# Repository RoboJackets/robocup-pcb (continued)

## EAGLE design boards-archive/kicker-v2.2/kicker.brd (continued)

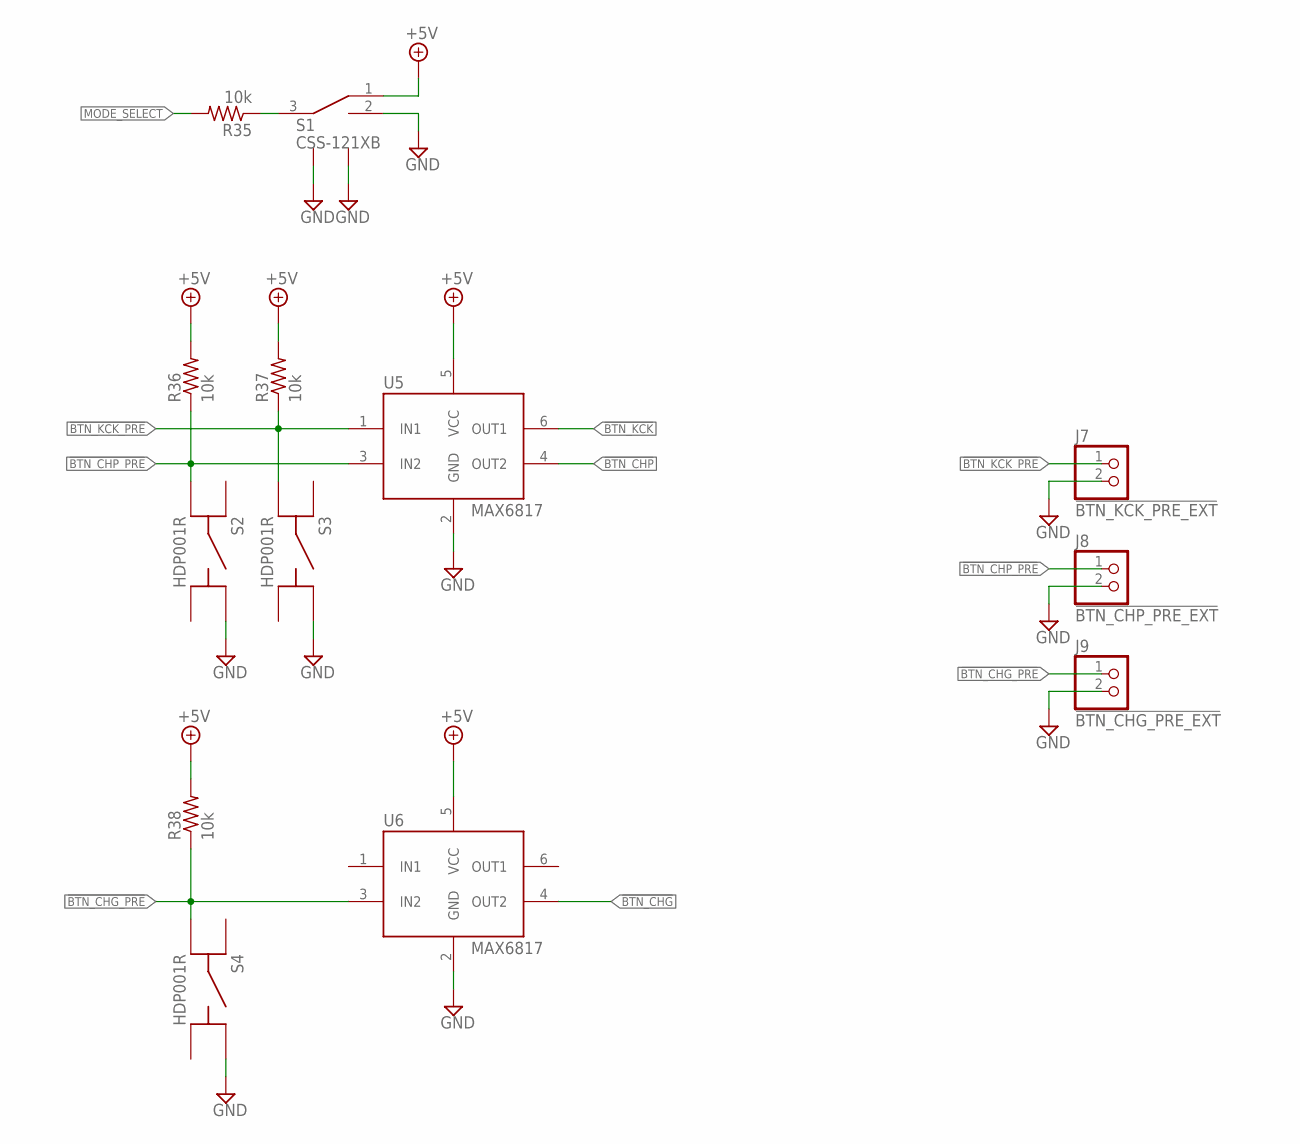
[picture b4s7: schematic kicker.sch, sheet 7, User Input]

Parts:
J7: !BTN_KCK_PRE_EXT; 1X2
J8: !BTN_CHP_PRE_EXT; 1X2
J9: !BTN_CHG_PRE_EXT; 1X2
R35, R36, R37, R38: 10k; R0603
S1: CSS-121XB
S2, S3, S4: HDP001R
U5, U6: MAX6817; SOT-23-6

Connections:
!BTN_CHG: U6.4 (OUT2); also elsewhere on the board
!BTN_CHG_PRE: J9.1, R38.1, S4.C (A2), U6.3 (IN2)
!BTN_CHP: U5.4 (OUT2); also elsewhere on the board
!BTN_CHP_PRE: J8.1, R36.1, S2.C (A2), U5.3 (IN2)
!BTN_KCK: U5.6 (OUT1); also elsewhere on the board
!BTN_KCK_PRE: J7.1, R37.1, S3.C (A2), U5.1 (IN1)
+5V: R36.2, R37.2, R38.2, S1.1 (A), U5.5 (VCC), U6.5 (VCC); also elsewhere on the board
GND: J7.2, J8.2, J9.2, S1.2 (B), S1.LEG1, S1.LEG4 (LEG2), S2.B (B1), S3.B (B1), S4.B (B1), U5.2 (GND), U6.2 (GND); also elsewhere on the board
MODE_SELECT: R35.2; also elsewhere on the board
unnamed: R35.1, S1.3 (COMMON)

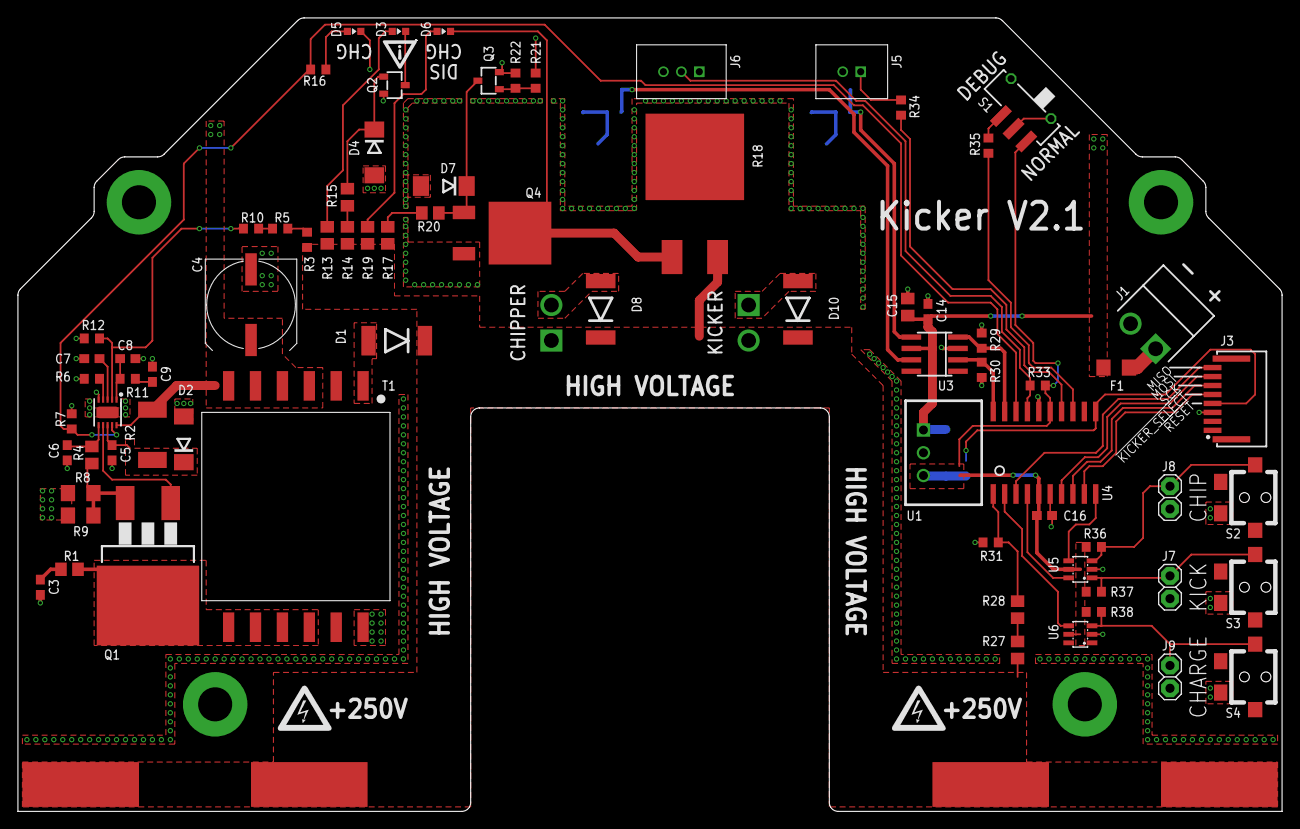
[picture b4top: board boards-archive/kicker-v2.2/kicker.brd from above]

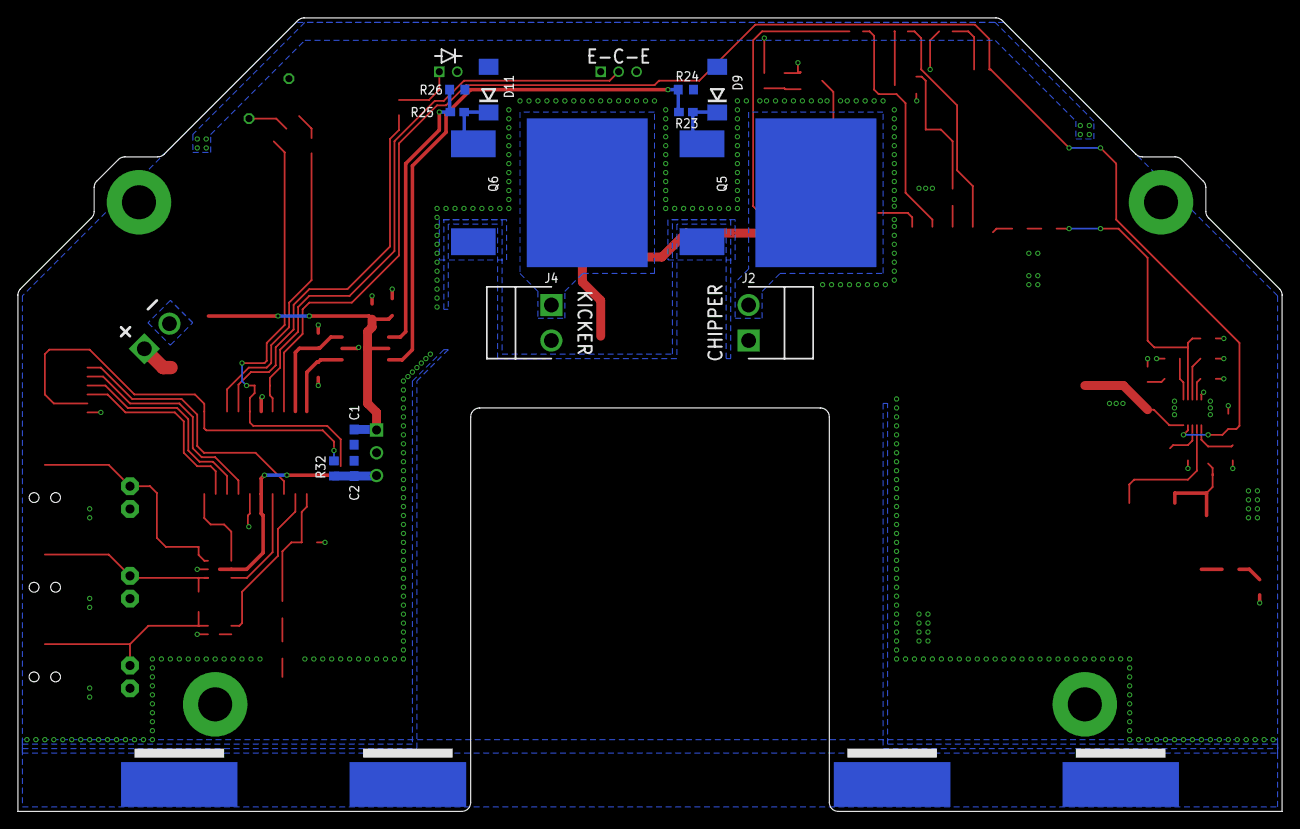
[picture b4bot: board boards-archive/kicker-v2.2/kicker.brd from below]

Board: 2 copper layers, 141.0 x 88.5 mm, 95 parts (13 on the bottom side), 56 nets.

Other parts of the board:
U$1, U$2: HV_WARNING
U$4: WARNING2

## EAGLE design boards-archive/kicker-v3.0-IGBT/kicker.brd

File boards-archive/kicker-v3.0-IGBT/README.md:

# Kicker Board

Charges a bank of capacitors to a high voltage and discharges into solenoid(s).

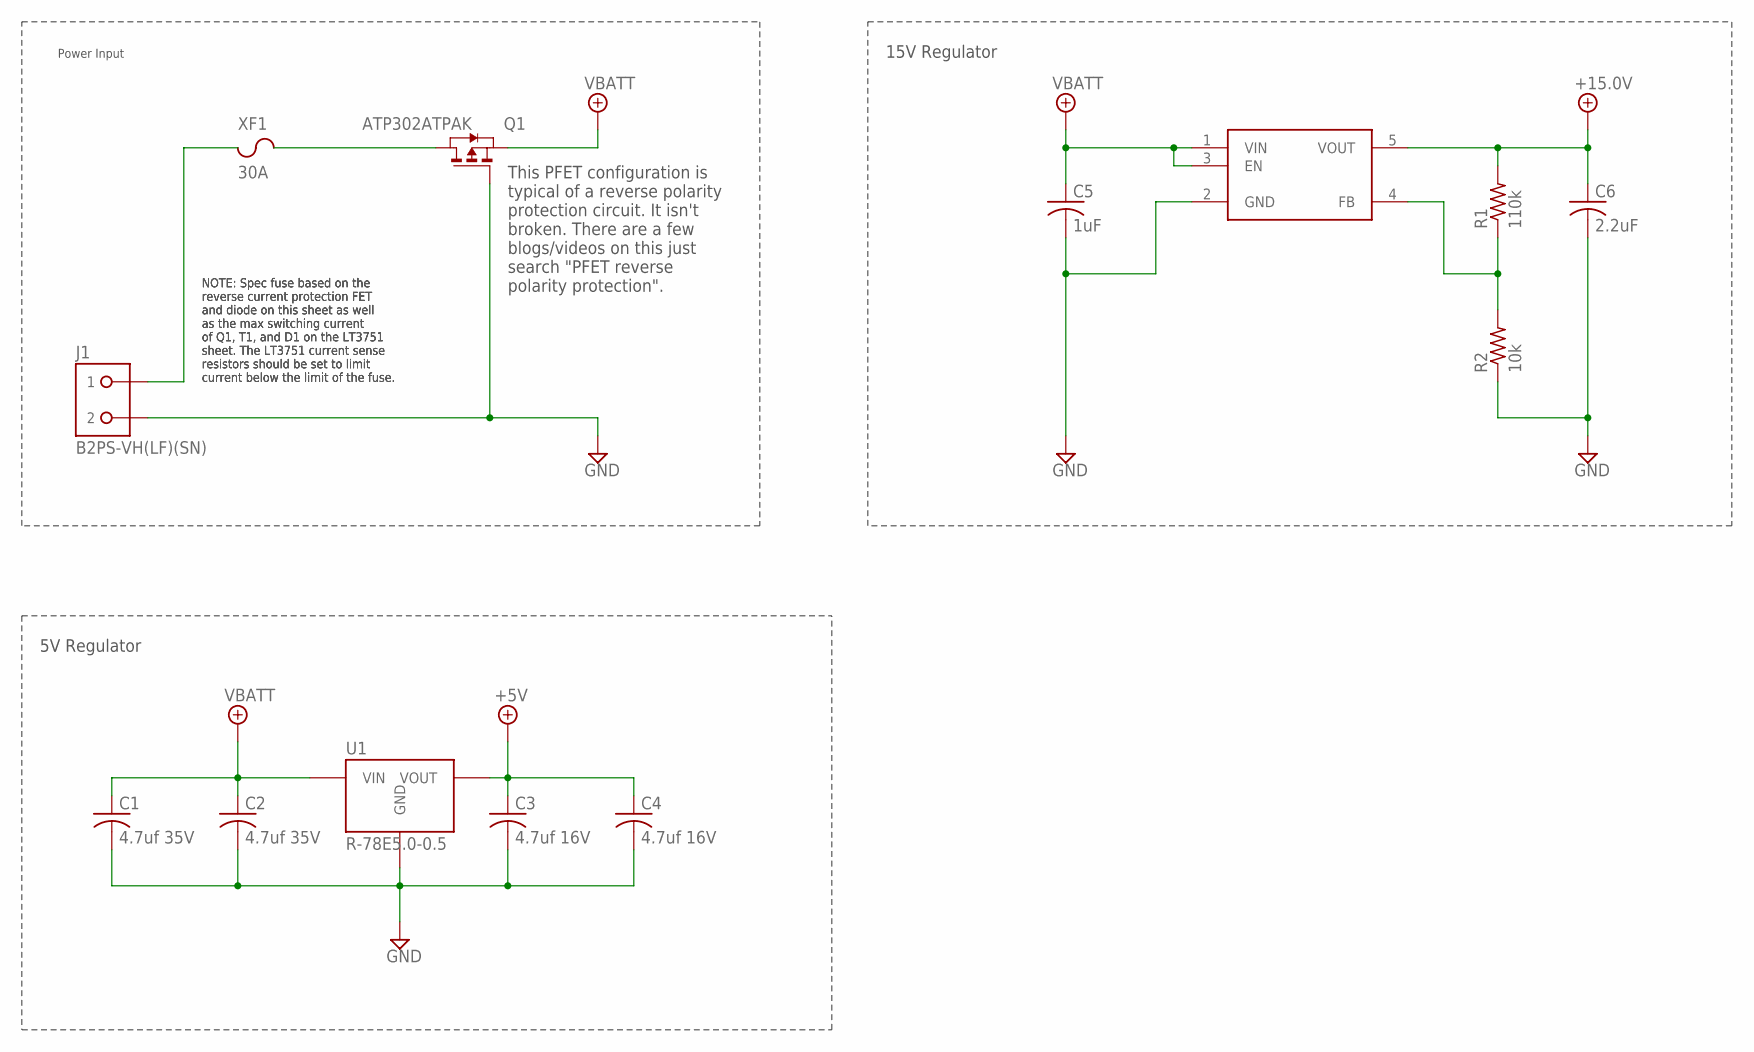
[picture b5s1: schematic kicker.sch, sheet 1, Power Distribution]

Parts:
C1, C2: 4.7uf 35V; C1210
C3, C4: 4.7uf 16V; C1210
C5: 1uF; C0603
C6: 2.2uF; C0603
J1: B2PS-VH(LF)(SN); B2PS-CENTERED
Q1: ATP302ATPAK; TO460P950X150-3
R1: 110k; R0603
R2: 10k; R0603
U1: R-78E5.0-0.5; R-78E
U2: 15V; SOT95P280X145-5
XF1: 30A; 3557-2

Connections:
+5V: C3.1, C4.1, U1.3 (VOUT); also elsewhere on the board
+15.0V: C6.1, R1.2, U2.5 (VOUT); also elsewhere on the board
GND: C1.2, C2.2, C3.2, C4.2, C5.2, C6.2, J1.2, Q1.1 (G), R2.1, U1.2 (GND), U2.2 (GND); also elsewhere on the board
unnamed: Q1.3 (D), XF1.3 (2), XF1.4 (2)
unnamed: R1.1, R2.2, U2.4 (FB)
unnamed: J1.1, XF1.1, XF1.2 (1)
VBATT: C1.1, C2.1, C5.1, Q1.2 (S), U1.1 (VIN), U2.1 (VIN), U2.3 (EN); also elsewhere on the board

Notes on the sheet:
Power Input
5V Regulator
NOTE: Spec fuse based on the reverse current protection FET and diode on this sheet as well as the max switching current of Q1, T1, and D1 on the LT3751 sheet. The LT3751 current sense resistors should be set to limit current below the limit of the fuse.
15V Regulator
This PFET configuration is typical of a reverse polarity protection circuit. It isn't broken. There are a few blogs/videos on this just search "PFET reverse polarity protection".

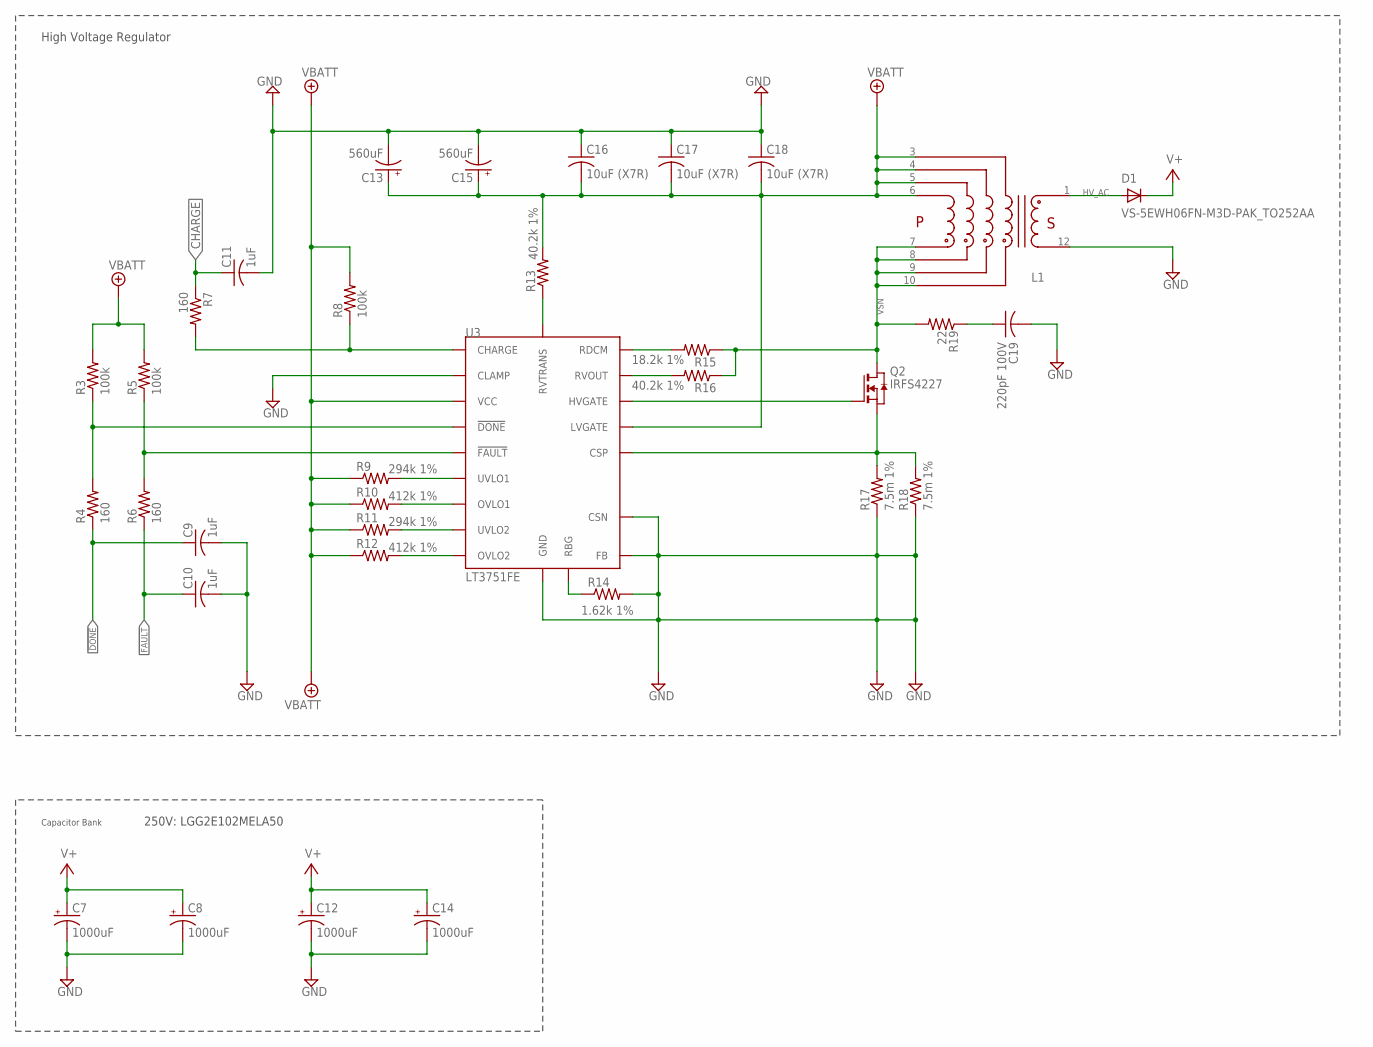
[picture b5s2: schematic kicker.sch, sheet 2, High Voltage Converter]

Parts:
C7, C8, C12, C14: 1000uF; EB25D
C9, C10, C11: 1uF; C0603
C13, C15: 560uF; E7,5-18
C16, C17, C18: 10uF (X7R); C1210
C19: 220pF 100V; C0603
D1: VS-5EWH06FN-M3D-PAK_TO252AA; TO460P990X239-3
L1: GA34XX-BLBL; SOP400P3370X1400-12
Q2: IRFS4227; D2PAK
R3, R5, R8: 100k; R0603
R4, R6, R7: 160; R0603
R9, R11: 294k 1%; R0805
R10, R12: 412k 1%; R0805
R13, R16: 40.2k 1%; R0805
R14: 1.62k 1%; R0805
R15: 18.2k 1%; R0805
R17, R18: 7.5m 1%; R2512
R19: 22; R0805
U3: LT3751FE; TSSOP-20_EP

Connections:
!DONE!: C9.1, R4.1; also elsewhere on the board
!DONE_LPF: R3.1, R4.2, U3.7 (!DONE); also elsewhere on the board
!FAULT!: C10.1, R6.1; also elsewhere on the board
!FAULT_LPF: R5.1, R6.2, U3.6 (!FAULT); also elsewhere on the board
CHARGE: C11.1, R7.1; also elsewhere on the board
CHARGE_LPF: R7.2, R8.1, U3.8 (CHARGE)
GND: C7.-, C8.-, C9.2, C10.2, C11.2, C12.-, C13.-, C14.-, C15.-, C16.1, C17.1, C18.1, C19.2, L1.12, R14.2, R17.1, R18.1, U3.9 (CLAMP), U3.10 (FB), U3.11 (CSN), U3.PAD (GND); also elsewhere on the board
HVGATE: Q2.1 (G), U3.15 (HVGATE)
HV_AC: D1.2 (A), L1.1
unnamed: R14.1, U3.16 (RBG)
unnamed: R13.1, U3.1 (RVTRANS)
unnamed: C19.1, R19.1
OVLO1: R10.2, U3.3 (OVLO1)
OVLO2: R12.2, U3.5 (OVLO2)
RDCM: R15.2, U3.20 (RDCM)
RVOUT: R16.2, U3.18 (RVOUT)
SENSE: Q2.3 (S), R17.2, R18.2, U3.12 (CSP)
UVLO1: R9.2, U3.2 (UVLO1)
UVLO2: R11.2, U3.4 (UVLO2)
V+: C7.+, C8.+, C12.+, C14.+, D1.3 (C); also elsewhere on the board
VBATT: C13.+, C15.+, C16.2, C17.2, C18.2, L1.3, L1.4, L1.5, L1.6, R3.2, R5.2, R8.2, R9.1, R10.1, R11.1, R12.1, R13.2, U3.13 (VCC), U3.14 (LVGATE); also elsewhere on the board
VSN: L1.7, L1.8, L1.9, L1.10, Q2.2 (D), R15.1, R16.1, R19.2

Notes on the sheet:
Capacitor Bank
High Voltage Regulator
250V: LGG2E102MELA50

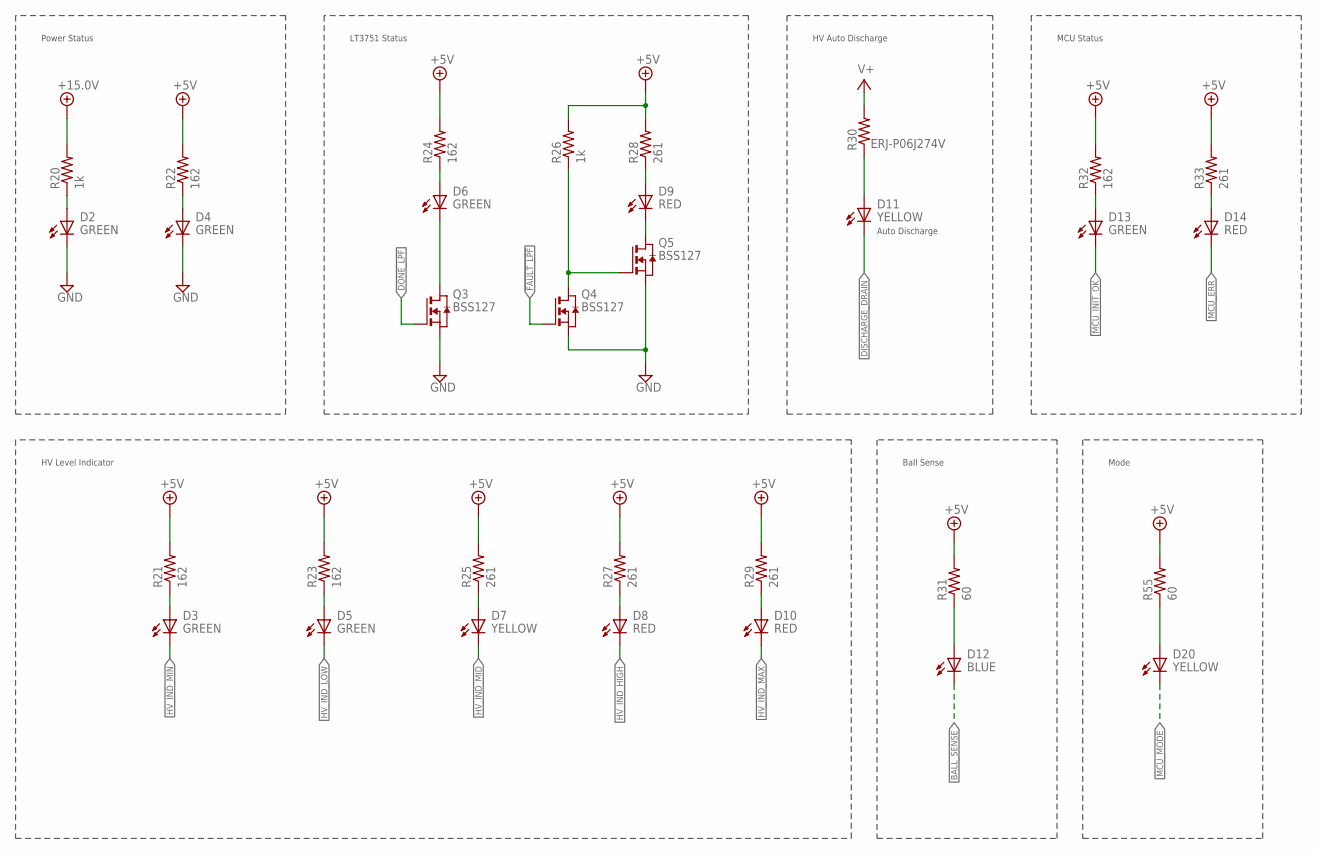
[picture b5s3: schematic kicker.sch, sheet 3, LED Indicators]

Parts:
D2, D3, D4, D5, D6, D13: GREEN; CHIP-LED0603
D7, D11, D20: YELLOW; CHIP-LED0603
D8, D9, D10, D14: RED; CHIP-LED0603
D12: BLUE; CHIP-LED0603
Q3, Q4, Q5: BSS127; SOT-23-3
R20, R26: 1k; R0603
R21, R22, R23, R24, R32: 162; R0603
R25, R27, R28, R29, R33: 261; R0603
R30: ERJ-P06J274V; R0805
R31, R55: 60; R0603

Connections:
!DONE_LPF: Q3.1 (G); also elsewhere on the board
!FAULT_LPF: Q4.1 (G); also elsewhere on the board
+5V: R21.2, R22.2, R23.2, R24.2, R25.2, R26.2, R27.2, R28.2, R29.2, R31.2, R32.2, R33.2, R55.2; also elsewhere on the board
+15.0V: R20.2; also elsewhere on the board
BALL_SENSE: D12.C (K); also elsewhere on the board
DISCHARGE_DRAIN: D11.C (K); also elsewhere on the board
GND: D2.C (K), D4.C (K), Q3.2 (S), Q4.2 (S), Q5.2 (S); also elsewhere on the board
HV_IND_HIGH: D8.C (K); also elsewhere on the board
HV_IND_LOW: D5.C (K); also elsewhere on the board
HV_IND_MAX: D10.C (K); also elsewhere on the board
HV_IND_MID: D7.C (K); also elsewhere on the board
HV_IND_MIN: D3.C (K); also elsewhere on the board
MCU_ERR: D14.C (K); also elsewhere on the board
MCU_INIT_OK: D13.C (K); also elsewhere on the board
MCU_MODE: D20.C (K); also elsewhere on the board
unnamed: D14.A, R33.1
unnamed: D13.A, R32.1
unnamed: D6.A, R24.1
unnamed: D3.A, R21.1
unnamed: D5.A, R23.1
unnamed: D7.A, R25.1
unnamed: D20.A, R55.1
unnamed: D4.A, R22.1
unnamed: D8.A, R27.1
unnamed: D2.A, R20.1
unnamed: Q4.3 (D), Q5.1 (G), R26.1
unnamed: D9.A, R28.1
unnamed: D9.C (K), Q5.3 (D)
unnamed: D11.A, R30.1
unnamed: D10.A, R29.1
unnamed: D6.C (K), Q3.3 (D)
unnamed: D12.A, R31.1
V+: R30.2; also elsewhere on the board

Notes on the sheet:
Power Status
LT3751 Status
Auto Discharge
HV Auto Discharge
MCU Status
HV Level Indicator
Ball Sense
Mode

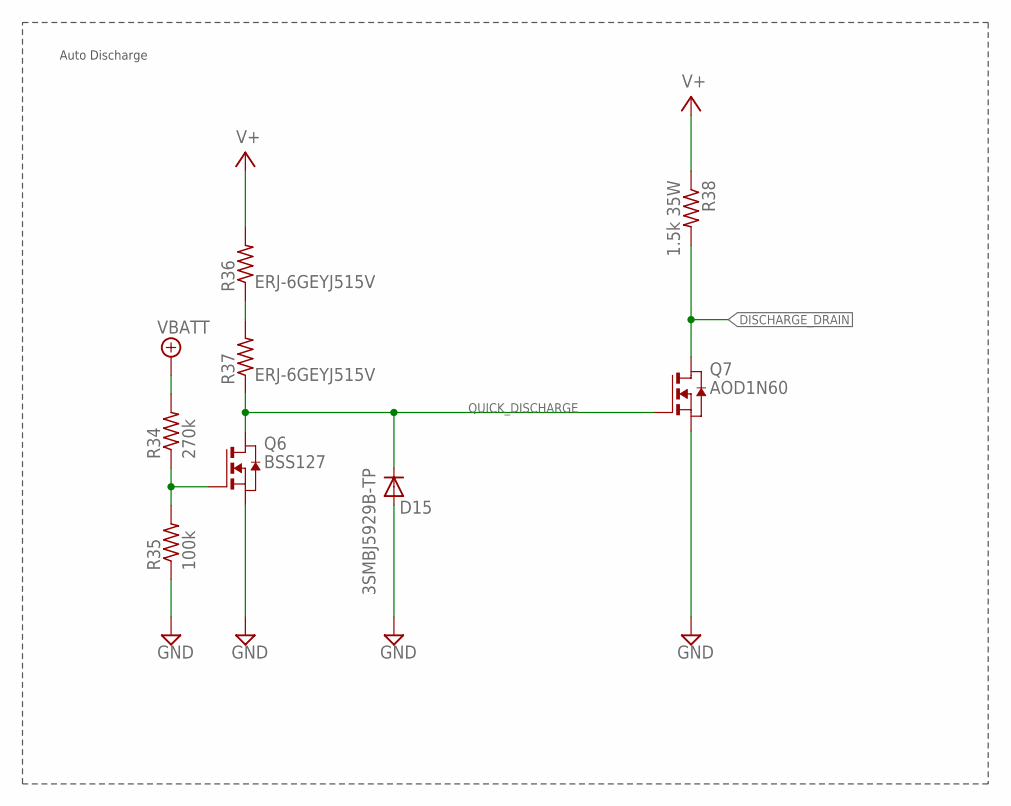
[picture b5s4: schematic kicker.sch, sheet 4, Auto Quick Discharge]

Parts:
D15: 3SMBJ5929B-TP; DO214AA
Q6: BSS127; SOT-23-3
Q7: AOD1N60; DPAK
R34: 270k; R0603
R35: 100k; R0603
R36, R37: ERJ-6GEYJ515V; R0805
R38: 1.5k 35W; TO508P1539X450-3

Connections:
DISCHARGE_DRAIN: Q7.FIN (D), R38.2 (PIN2); also elsewhere on the board
GND: D15.A, Q6.2 (S), Q7.3 (S), R35.1; also elsewhere on the board
unnamed: R36.1, R37.2
unnamed: Q6.1 (G), R34.1, R35.2
QUICK_DISCHARGE: D15.C, Q6.3 (D), Q7.1 (G), R37.1
V+: R36.2, R38.1 (PIN1); also elsewhere on the board
VBATT: R34.2; also elsewhere on the board

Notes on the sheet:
Auto Discharge

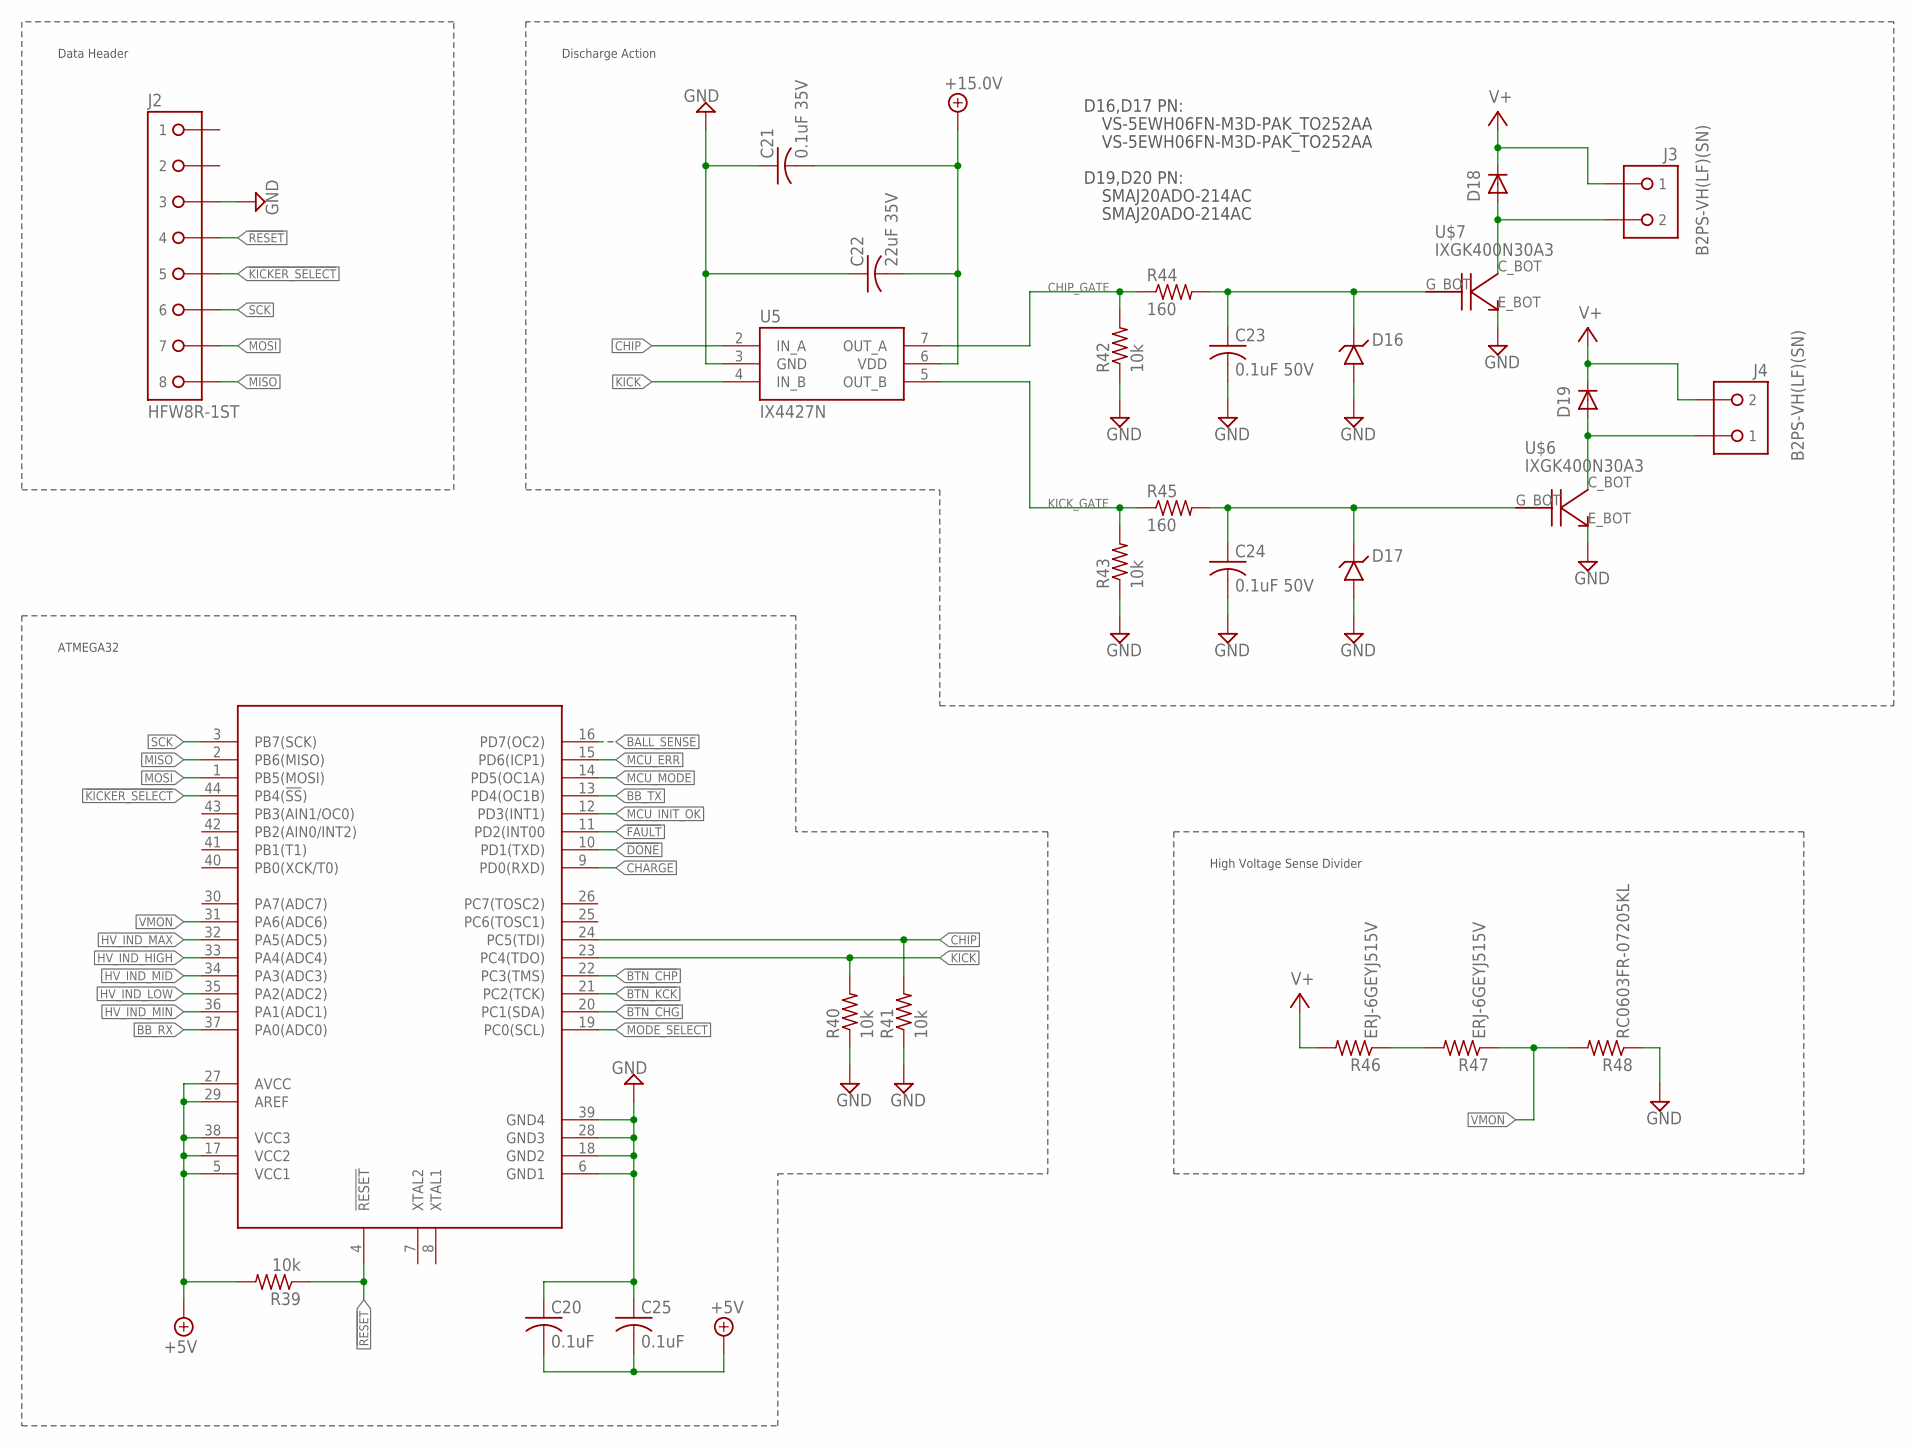
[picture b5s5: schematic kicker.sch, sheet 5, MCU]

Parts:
C20, C25: 0.1uF; C0603
C21: 0.1uF 35V; C0603
C22: 22uF 35V; C0805
C23, C24: 0.1uF 50V; C0603
D16, D17: SMAJ20ADO-214AC; RESM5226X262
D18, D19: VS-5EWH06FN-M3D-PAK_TO252AA; TO460P990X239-3
J2: HFW8R-1ST
J3, J4: B2PS-VH(LF)(SN); B2PS-CENTERED
R39, R40, R41, R42, R43: 10k; R0603
R44, R45: 160; R1206
R46, R47: ERJ-6GEYJ515V; R0805
R48: RC0603FR-07205KL; R0603
U4: AT32ATQFP44; QFP80P1200X1200X120-44
U5: IX4427N; SOIC-8
U$6, U$7: IXGK400N30A3; TO264

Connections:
!BTN_CHG: U4.20 (PC1(SDA)); also elsewhere on the board
!BTN_CHP: U4.22 (PC3(TMS)); also elsewhere on the board
!BTN_KCK: U4.21 (PC2(TCK)); also elsewhere on the board
!DONE!: U4.10 (PD1(TXD)); also elsewhere on the board
!FAULT!: U4.11 (PD2(INT00); also elsewhere on the board
!KICKER_SELECT: J2.5, U4.44 (PB4(!SS!))
!RESET: J2.4, R39.1, U4.4 (!RESET!)
+5V: C20.2, C25.2, R39.2, U4.5 (VCC1), U4.17 (VCC2), U4.27 (AVCC), U4.29 (AREF), U4.38 (VCC3); also elsewhere on the board
+15.0V: C21.2, C22.2, U5.6 (VDD); also elsewhere on the board
BALL_SENSE: U4.16 (PD7(OC2)); also elsewhere on the board
BB_RX: U4.37 (PA0(ADC0)); also elsewhere on the board
BB_TX: U4.13 (PD4(OC1B)); also elsewhere on the board
CHARGE: U4.9 (PD0(RXD)); also elsewhere on the board
CHIP: R41.2, U4.24 (PC5(TDI)), U5.2 (IN_A)
CHIPPER: D18.2 (A), J3.2, U$7.C_BOT (C)
CHIP_GATE: R42.2, R44.1, U5.7 (OUT_A)
GND: C20.1, C21.1, C22.1, C23.2, C24.2, C25.1, D16.1 (A), D17.1 (A), J2.3, R40.1, R41.1, R42.1, R43.1, R48.1, U4.6 (GND1), U4.18 (GND2), U4.28 (GND3), U4.39 (GND4), U5.3 (GND), U$6.E_BOT (E), U$7.E_BOT (E); also elsewhere on the board
HV_IND_HIGH: U4.33 (PA4(ADC4)); also elsewhere on the board
HV_IND_LOW: U4.35 (PA2(ADC2)); also elsewhere on the board
HV_IND_MAX: U4.32 (PA5(ADC5)); also elsewhere on the board
HV_IND_MID: U4.34 (PA3(ADC3)); also elsewhere on the board
HV_IND_MIN: U4.36 (PA1(ADC1)); also elsewhere on the board
KICK: R40.2, U4.23 (PC4(TDO)), U5.4 (IN_B)
KICKER: D19.2 (A), J4.1, U$6.C_BOT (C)
KICK_GATE: R43.2, R45.1, U5.5 (OUT_B)
MCU_ERR: U4.15 (PD6(ICP1)); also elsewhere on the board
MCU_INIT_OK: U4.12 (PD3(INT1)); also elsewhere on the board
MCU_MODE: U4.14 (PD5(OC1A)); also elsewhere on the board
MISO: J2.8, U4.2 (PB6(MISO))
MODE_SELECT: U4.19 (PC0(SCL)); also elsewhere on the board
MOSI: J2.7, U4.1 (PB5(MOSI))
unnamed: C23.1, D16.2 (C), R44.2, U$7.G_BOT (G)
unnamed: C24.1, D17.2 (C), R45.2, U$6.G_BOT (G)
unnamed: R46.1, R47.2
SCK: J2.6, U4.3 (PB7(SCK))
V+: D18.3 (C), D19.3 (C), J3.1, J4.2, R46.2; also elsewhere on the board
VMON: R47.1, R48.2, U4.31 (PA6(ADC6))

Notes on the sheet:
ATMEGA32
Data Header
Discharge Action
High Voltage Sense Divider
D16,D17 PN:
D19,D20 PN:
VS-5EWH06FN-M3D-PAK_TO252AA
SMAJ20ADO-214AC

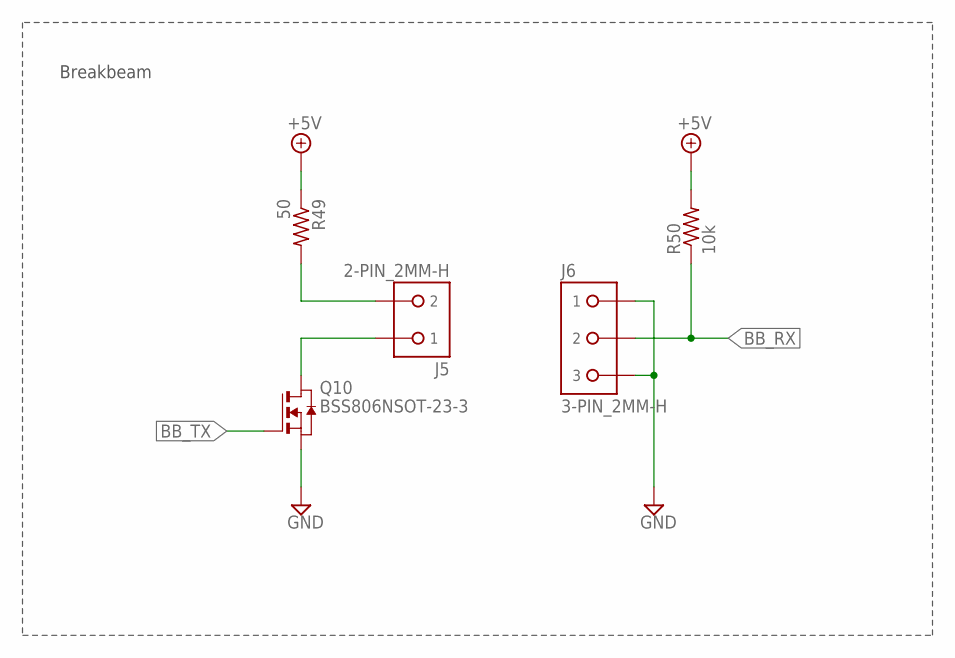
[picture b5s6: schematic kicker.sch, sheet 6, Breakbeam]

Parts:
J5: 2-PIN_2MM-H; 2MM-2-H
J6: 3-PIN_2MM-H; 2MM-3-H
Q10: BSS806NSOT-23-3; SOT95P240X110-3
R49: 50; R0603
R50: 10k; R0603

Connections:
+5V: R49.1, R50.2; also elsewhere on the board
BB_RX: J6.2, R50.1; also elsewhere on the board
BB_TX: Q10.1 (G); also elsewhere on the board
GND: J6.1, J6.3, Q10.2 (S); also elsewhere on the board
unnamed: J5.2, R49.2
unnamed: J5.1, Q10.3 (D)

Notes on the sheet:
Breakbeam

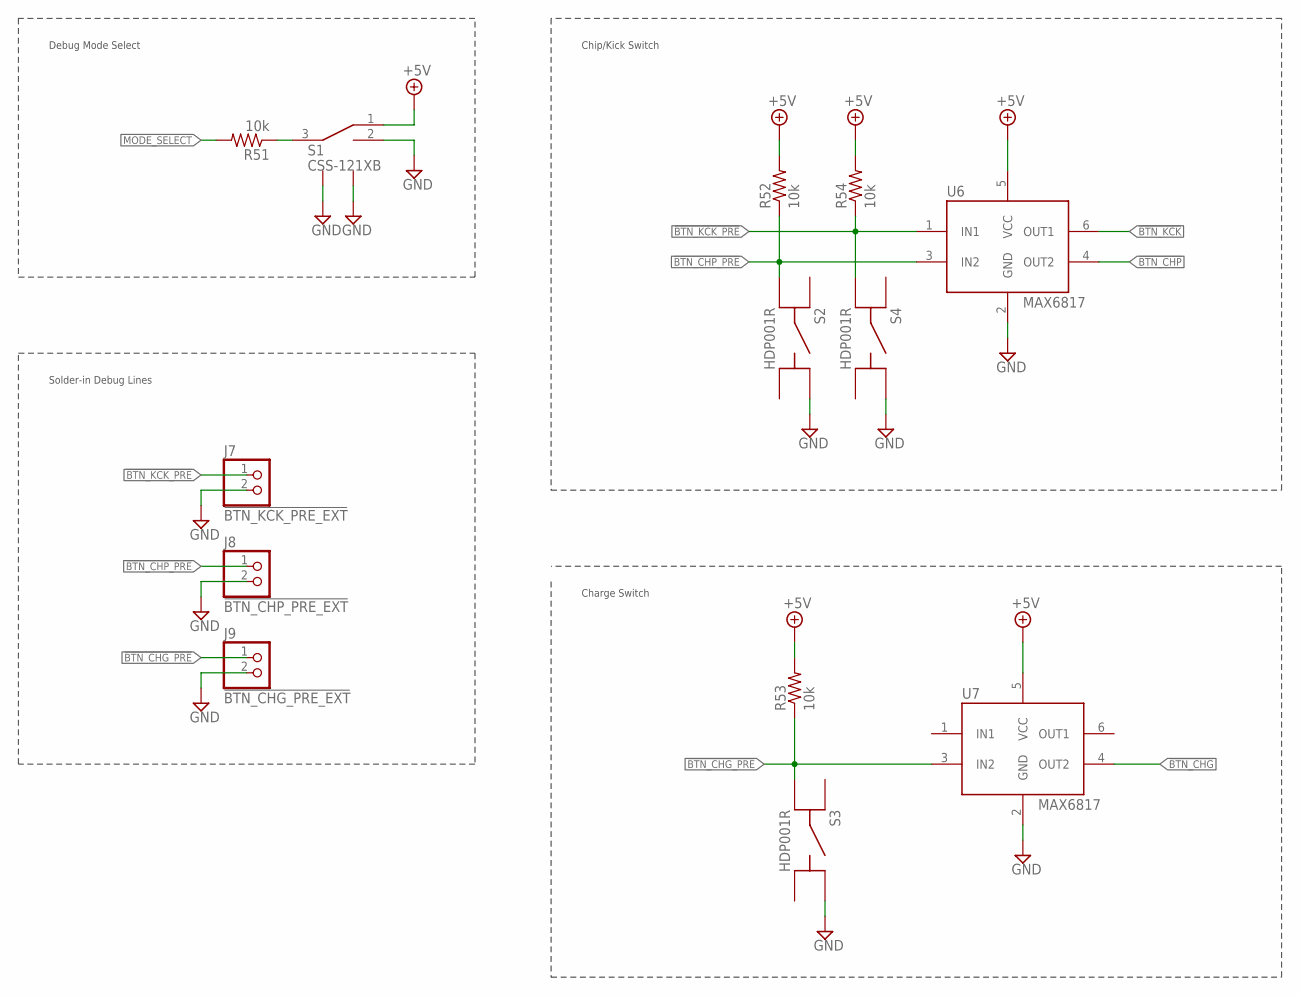
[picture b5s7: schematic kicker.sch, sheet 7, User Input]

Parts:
J7: !BTN_KCK_PRE_EXT; 1X2
J8: !BTN_CHP_PRE_EXT; 1X2
J9: !BTN_CHG_PRE_EXT; 1X2
R51, R52, R53, R54: 10k; R0603
S1: CSS-121XB
S2, S3, S4: HDP001R
U6, U7: MAX6817; SOT-23-6

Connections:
!BTN_CHG: U7.4 (OUT2); also elsewhere on the board
!BTN_CHG_PRE: J9.1, R53.1, S3.C (A2), U7.3 (IN2)
!BTN_CHP: U6.4 (OUT2); also elsewhere on the board
!BTN_CHP_PRE: J8.1, R52.1, S2.C (A2), U6.3 (IN2)
!BTN_KCK: U6.6 (OUT1); also elsewhere on the board
!BTN_KCK_PRE: J7.1, R54.1, S4.C (A2), U6.1 (IN1)
+5V: R52.2, R53.2, R54.2, S1.1 (A), U6.5 (VCC), U7.5 (VCC); also elsewhere on the board
GND: J7.2, J8.2, J9.2, S1.2 (B), S1.LEG1, S1.LEG4 (LEG2), S2.B (B1), S3.B (B1), S4.B (B1), U6.2 (GND), U7.2 (GND); also elsewhere on the board
MODE_SELECT: R51.2; also elsewhere on the board
unnamed: R51.1, S1.3 (COMMON)

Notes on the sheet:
Debug Mode Select
Chip/Kick Switch
Charge Switch
Solder-in Debug Lines
